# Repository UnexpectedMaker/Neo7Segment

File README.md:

# Neo7Segment Display Library
An API that lets you display numbers and letters on Neo7Segment RGB LED displays that are available from [tindie](https://www.tindie.com/products/seonr/neo7segment-display/)

You can find the Open Source hardware PCB design and Gerber files [here](https://github.com/UnexpectedMaker/Neo7Segment-Design-Files)

## Installing and Use
The downloaded code should be added to your arduino IDE libraries folder, and the library requires the [Adafruit NeoPixel library](https://github.com/adafruit/Adafruit_NeoPixel) for it to function.

To include the Neo7Segment library in your project:

    #include <Neo7Segment.h>

You can then initialise the display with the following line that includes the number of Neo7Segment digits and the GPIO to control them:

    Neo7Segment disp( 5, 4 );

You can also initialise the display with custom pixels per segment and pixel per decimal point

	#define PIXELS_DIGITS       5   // Number of digits
	#define PIXELS_PER_SEGMENT  4   // Pixels per segment - If you want more than 10 pixels per segment, modify the Neo7Segment.cpp
	#define PIXELS_PER_POINT    1   // Pixels per decimal point - CANNOT be higher than PIXELS_PER_SEGMENT
	#define PIXELS_PIN          4   // Pin number

	// Initalise the display with 5 Neo7Segment boards, 4 LEDs per segment, 1 decimal point LED, connected to GPIO 4
	Neo7Segment disp(PIXELS_DIGITS, PIXELS_PER_SEGMENT, PIXELS_PER_POINT, PIXELS_PIN);

You then start the display with the bebin method, passing the brightness:

    disp.Begin(20);

The you simply pass the display the String you would like displayed and a color:

    disp.DisplayText( "1234", disp.Color( 255,0,0) );
    
# Back me on Patreon?
I love making and designing projects but sharing open source projects takes a lot of thought and time. I do it because I think it’s important to share knowledge and give back to the community like many have done before me.

If you find this project useful or want to see more open source projects like it, please consider backing me on Patreon to say thanks!

# Unexpected Maker
http://youtube.com/c/unexpectedmaker

http://twitter.com/unexpectedmaker

https://www.facebook.com/unexpectedmaker/

https://www.instagram.com/unexpectedmaker/

https://www.tindie.com/stores/seonr/

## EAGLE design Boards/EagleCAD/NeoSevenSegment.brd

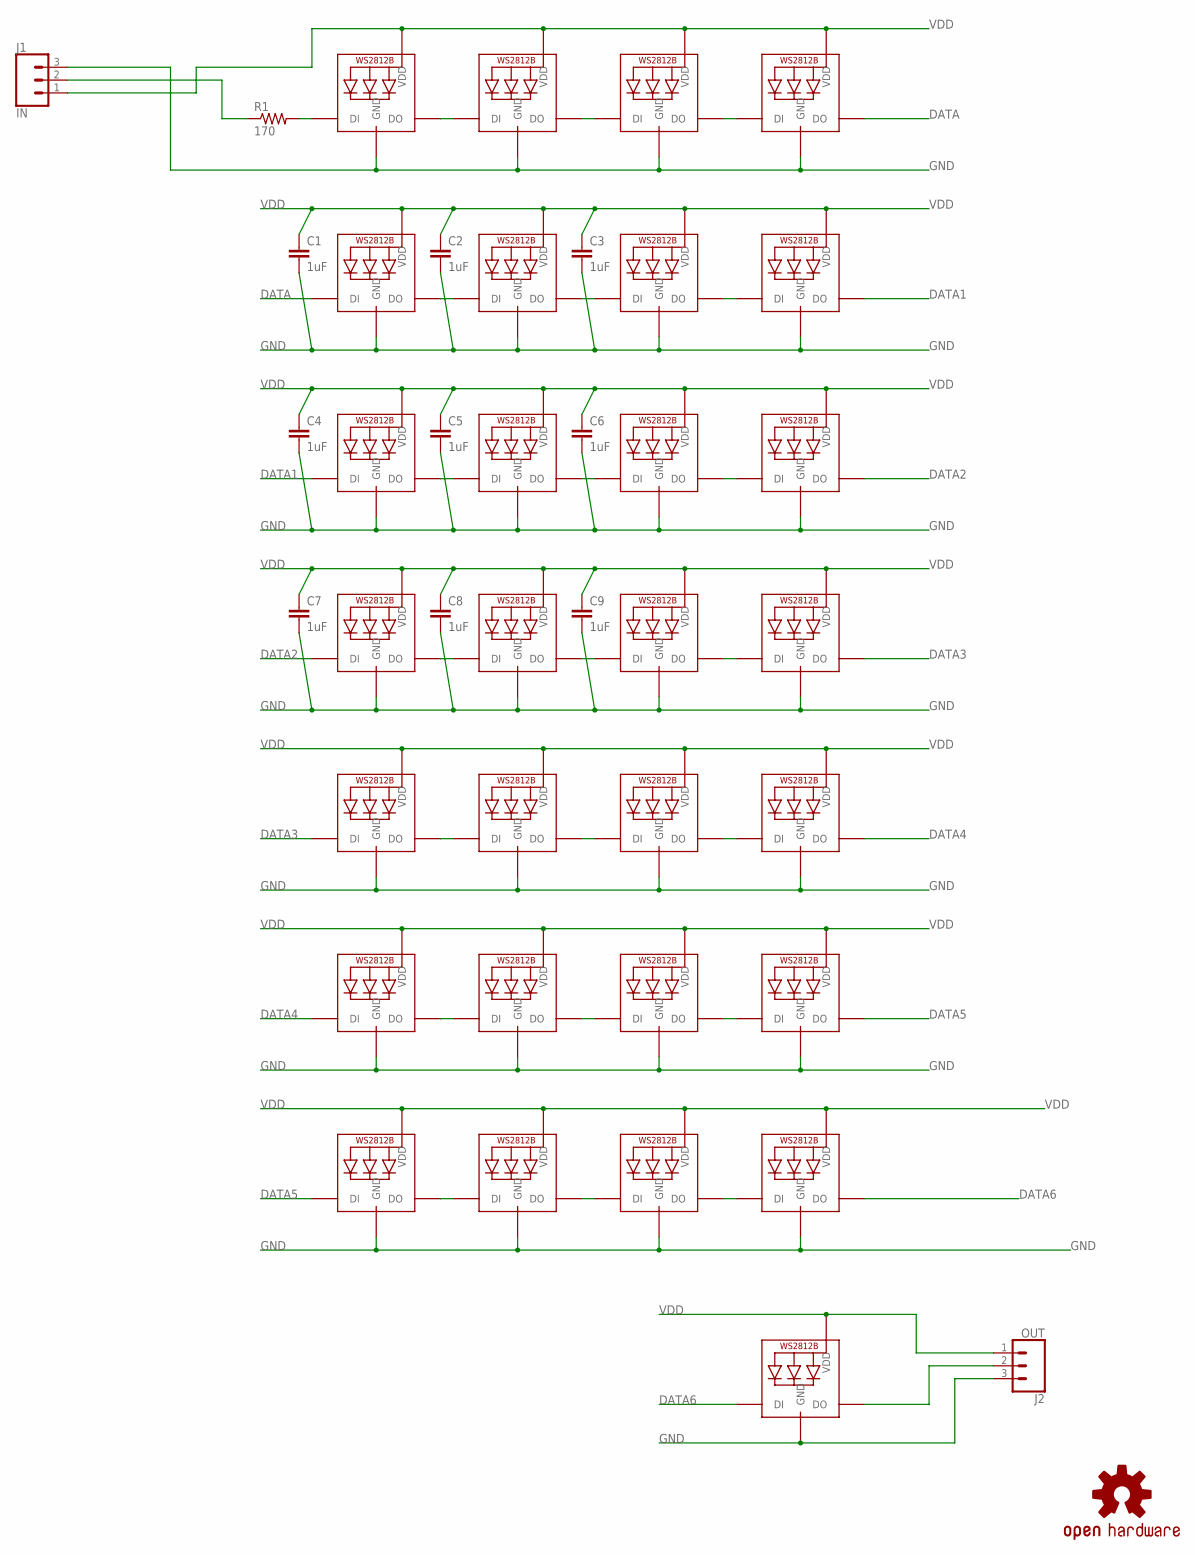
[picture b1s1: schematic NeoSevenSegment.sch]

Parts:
C1, C2, C3, C4, C5, C6, C7, C8, C9: 1uF; C0805
J1: IN; 1X03_LONGPADS
J2: OUT; 1X03_LONGPADS
LED1, LED2, LED3, LED4, LED5, LED6, LED7, LED8, LED9, LED10, LED11, LED12, LED13, LED14, LED15, LED16, LED17, LED18, LED19, LED20, LED21, LED22, LED23, LED24, LED25, LED26, LED27, LED28: WS2812B_5050N; WS2812B-NARROW
LED29: RGB 3535; LED3535
LOGO1: OSHW-LOGOM; OSHW-LOGO-M
R1: 170; R0805

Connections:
DATA: LED4.2-DOUT (DO), LED5.4-DIN (DI)
DATA1: LED8.2-DOUT (DO), LED9.4-DIN (DI)
DATA2: LED12.2-DOUT (DO), LED13.4-DIN (DI)
DATA3: LED16.2-DOUT (DO), LED17.4-DIN (DI)
DATA4: LED20.2-DOUT (DO), LED21.4-DIN (DI)
DATA5: LED24.2-DOUT (DO), LED25.4-DIN (DI)
DATA6: LED28.2-DOUT (DO), LED29.1 (DI)
DATA_OUT: J2.2, LED29.3 (DO)
DI: J1.2, R1.1
DI_R: LED1.4-DIN (DI), R1.2
GND: C1.2, C2.2, C3.2, C4.2, C5.2, C6.2, C7.2, C8.2, C9.2, J1.3, J2.3, LED1.3-GND (GND), LED2.3-GND (GND), LED3.3-GND (GND), LED4.3-GND (GND), LED5.3-GND (GND), LED6.3-GND (GND), LED7.3-GND (GND), LED8.3-GND (GND), LED9.3-GND (GND), LED10.3-GND (GND), LED11.3-GND (GND), LED12.3-GND (GND), LED13.3-GND (GND), LED14.3-GND (GND), LED15.3-GND (GND), LED16.3-GND (GND), LED17.3-GND (GND), LED18.3-GND (GND), LED19.3-GND (GND), LED20.3-GND (GND), LED21.3-GND (GND), LED22.3-GND (GND), LED23.3-GND (GND), LED24.3-GND (GND), LED25.3-GND (GND), LED26.3-GND (GND), LED27.3-GND (GND), LED28.3-GND (GND), LED29.4 (GND)
unnamed: LED9.2-DOUT (DO), LED10.4-DIN (DI)
unnamed: LED10.2-DOUT (DO), LED11.4-DIN (DI)
unnamed: LED11.2-DOUT (DO), LED12.4-DIN (DI)
unnamed: LED1.2-DOUT (DO), LED2.4-DIN (DI)
unnamed: LED2.2-DOUT (DO), LED3.4-DIN (DI)
unnamed: LED3.2-DOUT (DO), LED4.4-DIN (DI)
unnamed: LED13.2-DOUT (DO), LED14.4-DIN (DI)
unnamed: LED14.2-DOUT (DO), LED15.4-DIN (DI)
unnamed: LED15.2-DOUT (DO), LED16.4-DIN (DI)
unnamed: LED17.2-DOUT (DO), LED18.4-DIN (DI)
unnamed: LED18.2-DOUT (DO), LED19.4-DIN (DI)
unnamed: LED5.2-DOUT (DO), LED6.4-DIN (DI)
unnamed: LED6.2-DOUT (DO), LED7.4-DIN (DI)
unnamed: LED7.2-DOUT (DO), LED8.4-DIN (DI)
unnamed: LED19.2-DOUT (DO), LED20.4-DIN (DI)
unnamed: LED21.2-DOUT (DO), LED22.4-DIN (DI)
unnamed: LED22.2-DOUT (DO), LED23.4-DIN (DI)
unnamed: LED23.2-DOUT (DO), LED24.4-DIN (DI)
S1: LED25.2-DOUT (DO), LED26.4-DIN (DI)
S2: LED26.2-DOUT (DO), LED27.4-DIN (DI)
S3: LED27.2-DOUT (DO), LED28.4-DIN (DI)
VDD: C1.1, C2.1, C3.1, C4.1, C5.1, C6.1, C7.1, C8.1, C9.1, J1.1, J2.1, LED1.1-VDD (VDD), LED2.1-VDD (VDD), LED3.1-VDD (VDD), LED4.1-VDD (VDD), LED5.1-VDD (VDD), LED6.1-VDD (VDD), LED7.1-VDD (VDD), LED8.1-VDD (VDD), LED9.1-VDD (VDD), LED10.1-VDD (VDD), LED11.1-VDD (VDD), LED12.1-VDD (VDD), LED13.1-VDD (VDD), LED14.1-VDD (VDD), LED15.1-VDD (VDD), LED16.1-VDD (VDD), LED17.1-VDD (VDD), LED18.1-VDD (VDD), LED19.1-VDD (VDD), LED20.1-VDD (VDD), LED21.1-VDD (VDD), LED22.1-VDD (VDD), LED23.1-VDD (VDD), LED24.1-VDD (VDD), LED25.1-VDD (VDD), LED26.1-VDD (VDD), LED27.1-VDD (VDD), LED28.1-VDD (VDD), LED29.2 (VDD)

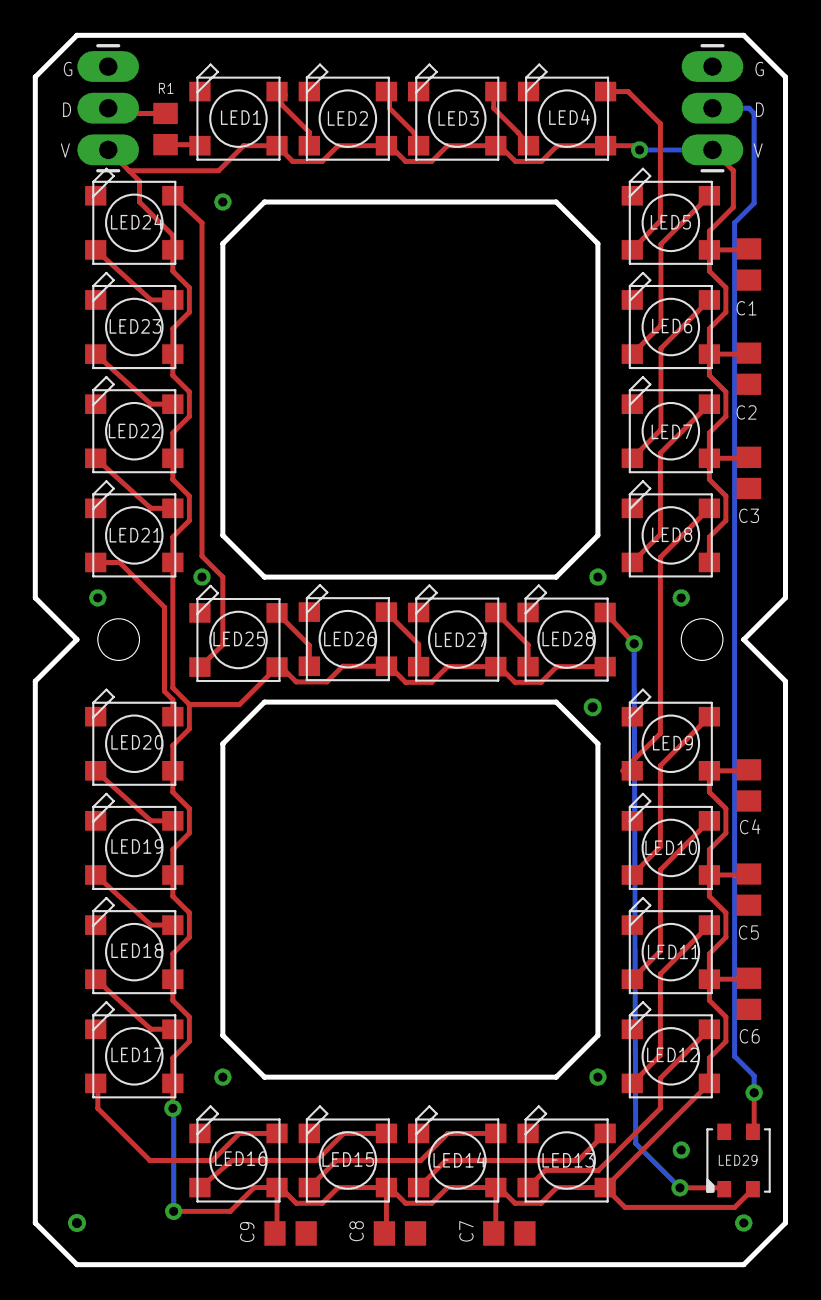
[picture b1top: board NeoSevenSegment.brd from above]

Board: 2 copper layers, 45.7 x 74.9 mm, 42 parts (1 on the bottom side), 33 nets.

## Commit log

2018-04-08 Initial code and PCB files commit
2018-04-08 Fixed formatting in readme
2018-04-08 Moved design files out so they can go into their own repository Moved library files to the root of the repositry
2018-04-08 added design files link in readme
2018-04-25 Fixed issue due to change in how Adafruit Neopixel library was initliased post compile time.
2018-04-25 Removed RTC library from example code
2018-05-26 Remove redundant paragraph text from library.properties
    The Arduino IDE's Library Manager displays the text defined in the library.properties paragraph field immediately after the sentence text so it's not desirable to duplicate the sentence text in parag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
2018-07-25 Update README.md
    Added donate button
2019-01-06 Upgraded to variable pixels per segment/decimal
    I reworked the neo7segment library for custom sized digits and corrected few bugs.
    I was wondering if you’d be interested in updating your repository? Otherwise I’ll post it on my own GitHub, but I really think it would be good for everyone.
    -Allows to determine the number of pixels per segment
    -Allows to determine the number of pixels per decimal point.
    -You can call the library with 0 decimal points and it serves the same purpose as removing the #define USEDP
    -Also corrected few bugs in the original library that had decimal point to fail
2019-01-06 Added fallback
    Forgot the fallback constructor for backward compatibility
2019-01-06 Update the readme
2019-01-06 Text error
2019-01-06 Indent error
2019-01-06 Update comments
2019-01-20 Updated version information before tagging
2020-01-08 Specify library dependencies in library.properties
    Specifying the library dependencies in the depends field of library.properties causes the Arduino Library Manager (Arduino IDE 1.8.10 and newer) to offer to install any missing dependencies during in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
2020-04-20 Modification to display text and added character
    - Modifications to allow lower and uppercase character in the same string (e.g: HEllo instead of HELLO or hEllo)
    - If lowercase character doesn't exist, upper case is used (e.g.: hEllo)
    - If user sets ForceUppercase(true), it would give HELLO
    - Modifications to letters bit assignment for better display
    - Added underscore "_" to list
    TESTED and working on real life display

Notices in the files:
parts and their libraries:
SparkFun-Connectors: Licensing: Creative Commons ShareAlike 4.0 International - https://creativecommons.org/licenses/by-sa/4.0
